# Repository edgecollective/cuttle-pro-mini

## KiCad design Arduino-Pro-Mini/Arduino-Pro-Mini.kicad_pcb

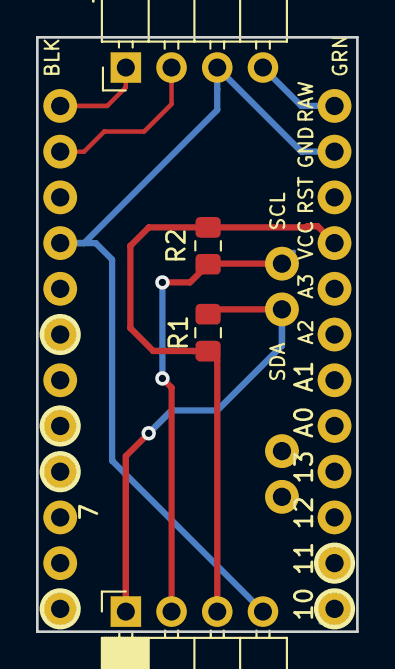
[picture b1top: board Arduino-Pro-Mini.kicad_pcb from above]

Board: 2 copper layers, 17.8 x 33.0 mm, 8 parts (0 on the bottom side), 8 nets.

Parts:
J1: Conn_01x04_Male; PinHeader_1x04_P2.54mm_Horizontal
J2: Conn_01x04_Female; PinSocket_1x04_P2.54mm_Horizontal
JP2, JP3: M02PTH; 1X02
JP6, JP7: M12PTH; 1X12
R1, R2: R; R_0805_2012Metric_Pad1.15x1.40mm_HandSolder

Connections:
3.3V: J2.3, JP6.4, R1.1, R2.1
/RESET: JP6.3, JP7.10
GND: J1.3, J2.4, JP6.2, JP7.9
RX: J1.2, JP7.11
SCL: J2.2, JP2.2, R2.2
SDA: J2.1, JP2.1, R1.2
TX: J1.1, JP7.12
VIN: J1.4, JP6.1
